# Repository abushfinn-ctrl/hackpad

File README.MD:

# **FusionPad**
FusionPad is a 2x4 key macropad with a rotary encoder it uses KMK firmware. I decided to make this because I recently switch from a logitech G502 with lots of buttons to a Bambu custom 3d printed mouse with no extra buttons. I then was able to have my fusions commands on my mouse so I decided to make a macropad specifically for Fusion. 

Features:
Two part 3d printer case
EC11 Rotary encoder for volume (can be changed for zoom)
8 Keys

# **How to build:**
Once your PCB arrives you can start soldering all the componenet into the correct spots, then you plug the Hackpad in and add the firmware. Easy Peasy.

# **CAD Model:**
The case screws together using 4 M3 bolts and headset inserts. One on each corner

# **PCB**
Here's my PCB! It was made in KiCad.\

# **PCB Schematic** 
Messy I know\

I used MX_V2 for the keyswitch footprints.

# **Firmware Overview**
My hackpad uses KMK firmware for everything.

The rotary encoder changes volume. Click to mute
Can be changed to zoom in and out
The 8 keys currently act as common key shortcuts I use in fusion.

# **BOM:**
Here should be everything you need to make this hackpad

8x Cherry MX Switches\
8x DSA Keycaps\
4x M3x5x4 Heatset inserts\
4x M3x16mm SHCS Bolts\
1x EC11 Rotary Encoder\
1x XIAO RP2040\
1x Case (3d printed)

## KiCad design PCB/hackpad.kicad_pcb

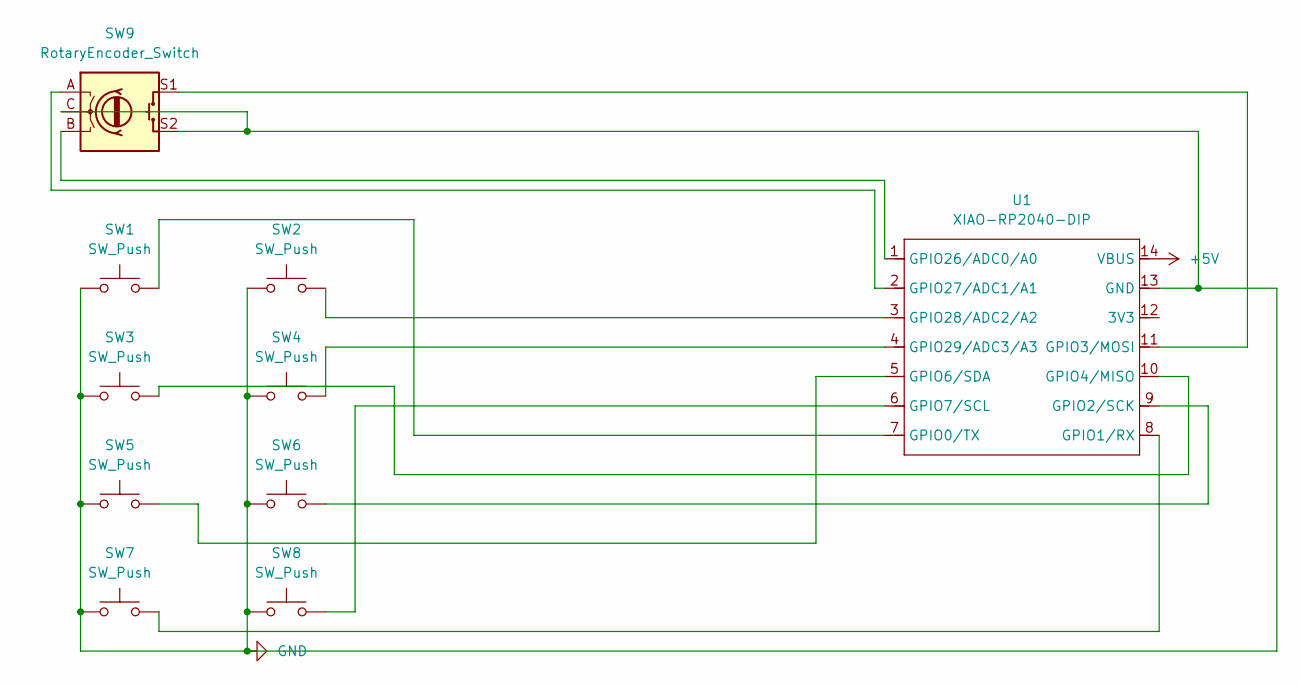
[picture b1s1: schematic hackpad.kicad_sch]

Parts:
SW1, SW2, SW3, SW4, SW5, SW6, SW7, SW8: SW_Push; SW_Cherry_MX_1.00u_PCB
SW9: RotaryEncoder_Switch; RotaryEncoder_Alps_EC11E-Switch_Vertical_H20mm
U1: XIAO-RP2040-DIP

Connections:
+5V: U1.14 (VBUS)
GND: SW1.1, SW2.1, SW3.1, SW4.1, SW5.1, SW6.1, SW7.1, SW8.1, SW9.C, SW9.S2, U1.13 (GND)
unnamed: SW1.2, U1.7 (GPIO0/TX)
unnamed: SW7.2, U1.8 (GPIO1/RX)
unnamed: SW6.2, U1.9 (GPIO2/SCK)
unnamed: SW9.S1, U1.11 (GPIO3/MOSI)
unnamed: SW3.2, U1.10 (GPIO4/MISO)
unnamed: SW5.2, U1.5 (GPIO6/SDA)
unnamed: SW8.2, U1.6 (GPIO7/SCL)
unnamed: SW9.B, U1.1 (GPIO26/ADC0/A0)
unnamed: SW9.A, U1.2 (GPIO27/ADC1/A1)
unnamed: SW2.2, U1.3 (GPIO28/ADC2/A2)
unnamed: SW4.2, U1.4 (GPIO29/ADC3/A3)

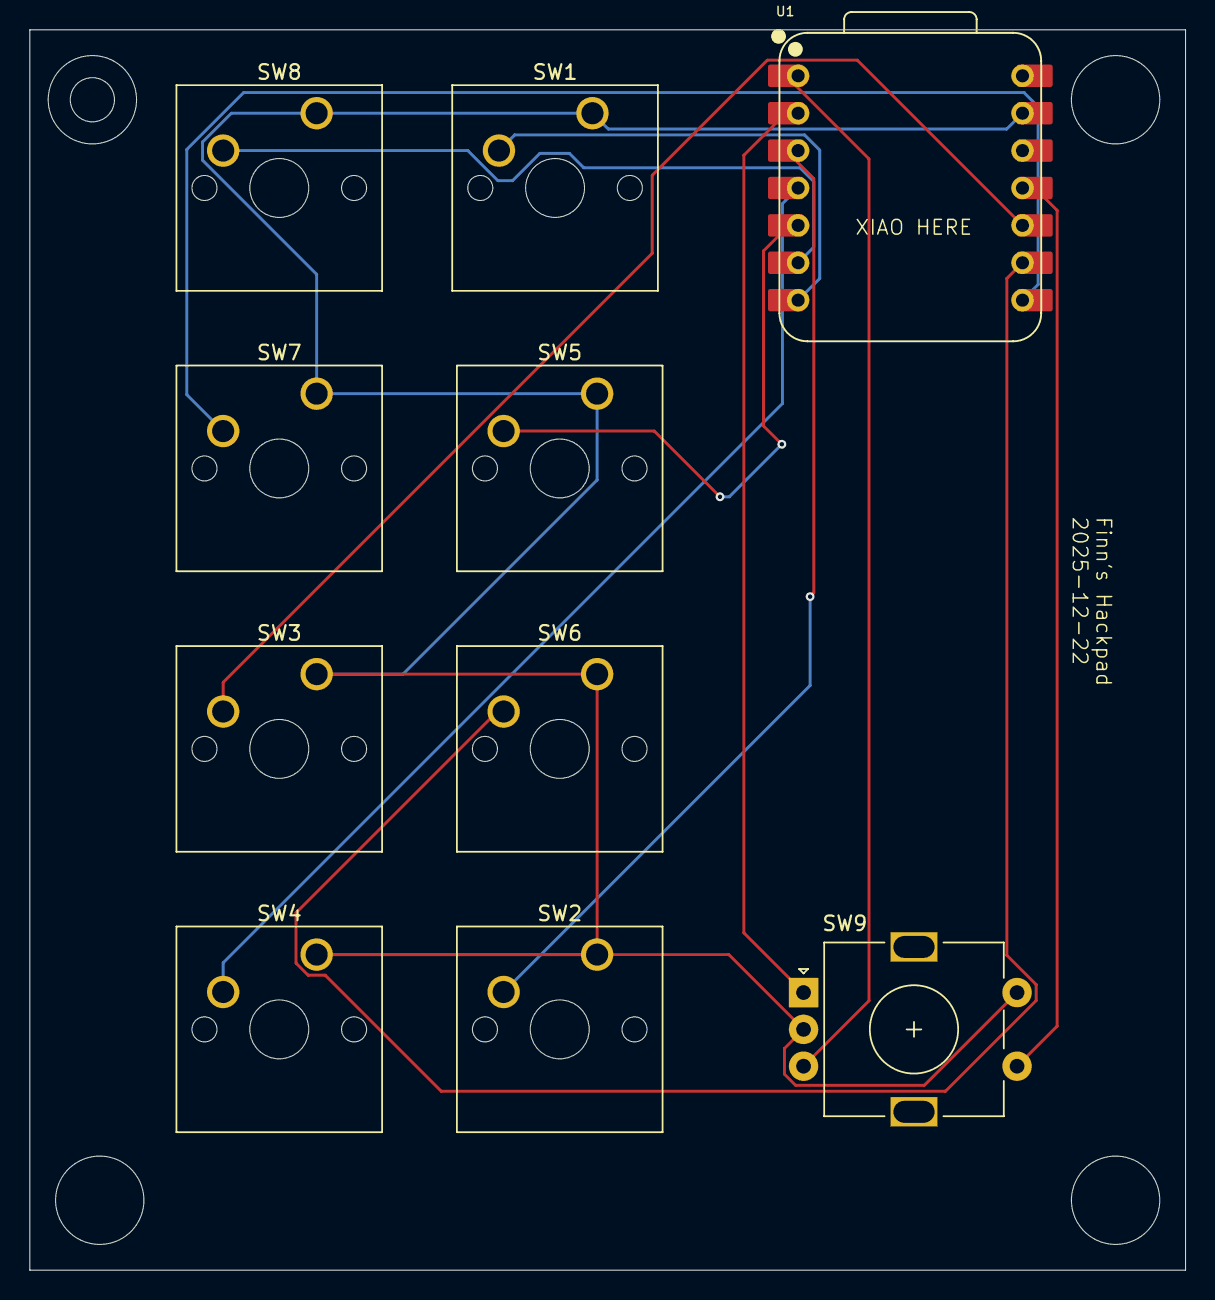
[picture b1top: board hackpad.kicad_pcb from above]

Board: 2 copper layers, 78.5 x 84.2 mm, 10 parts (0 on the bottom side), 12 nets.

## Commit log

2025-12-22 Create b
2025-12-22 Create _
